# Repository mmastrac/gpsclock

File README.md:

========

Simple GPS clock project based on simple components from Adafruit and eBay. This consists of a number of components:

  * A backpack for the Adafruit KWA-221 2.3" digit based on the TLC-5920NT (KiCad PCB project)

  * An Arduino project that reads GPS time from the Adafruit GPS adapter and pushes it out to backpack

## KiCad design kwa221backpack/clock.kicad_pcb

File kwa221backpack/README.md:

TODO:

  * Contribute TLC-5940NT back to open-projects
  * Move all routed traces underneath footprint of LED

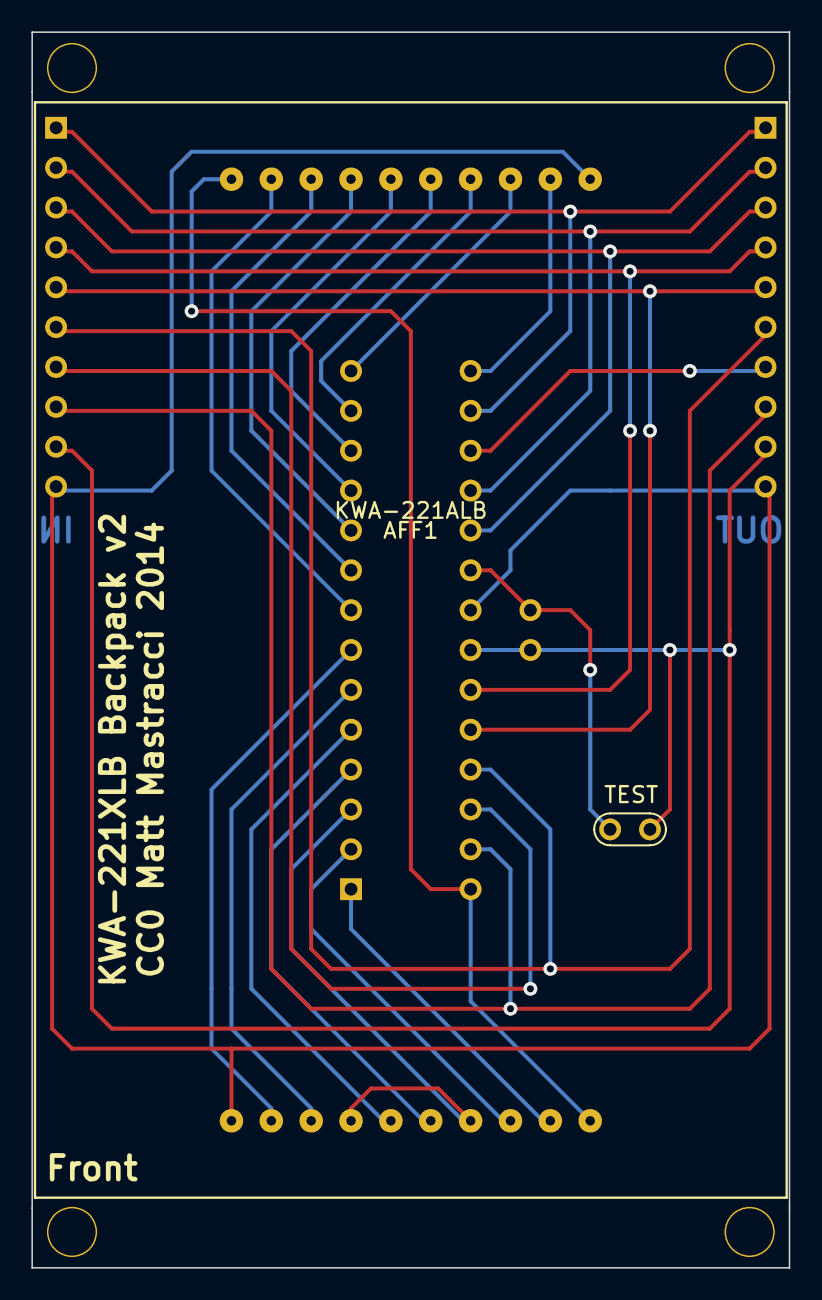
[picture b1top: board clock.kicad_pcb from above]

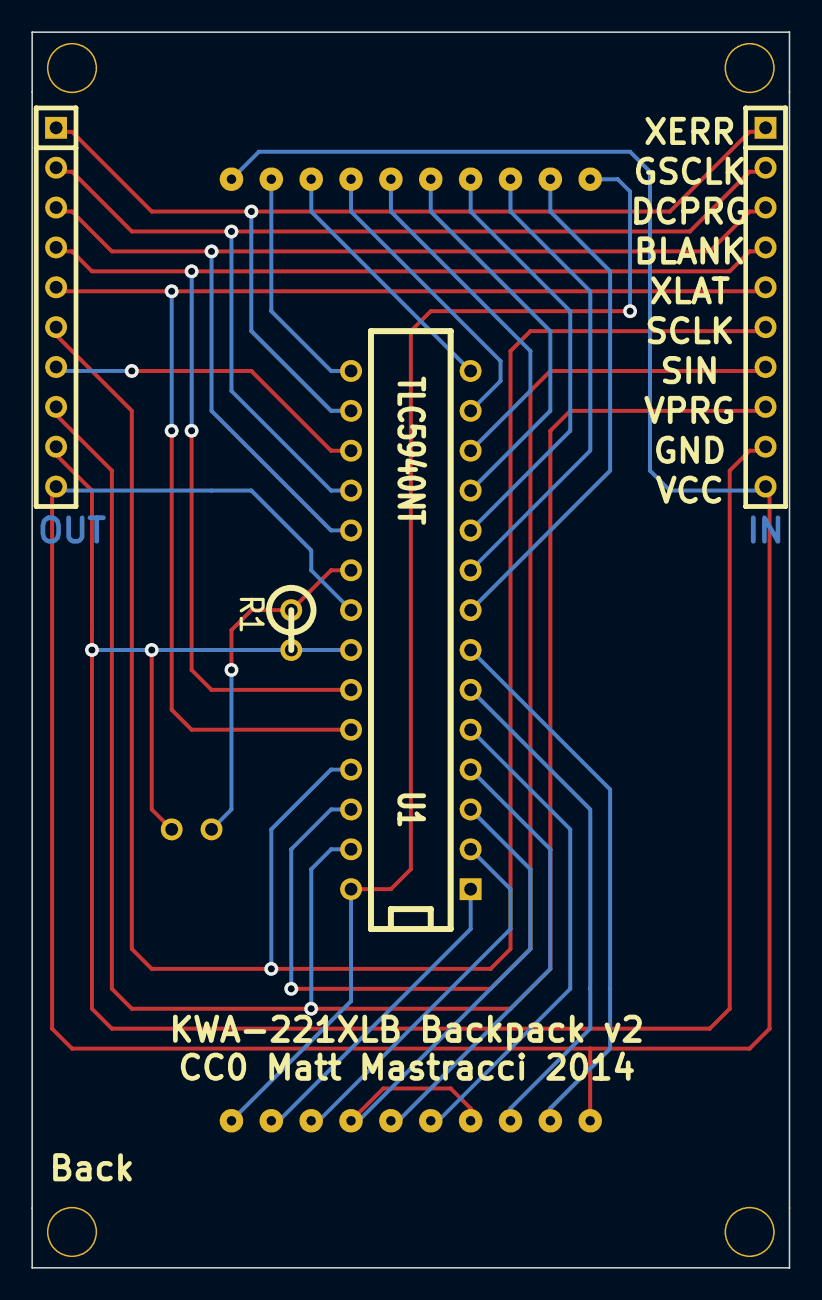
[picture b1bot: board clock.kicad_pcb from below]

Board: 2 copper layers, 48.3 x 78.7 mm, 10 parts (4 on the bottom side), 28 nets.

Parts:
AFF1: KWA-221ALB; KWA-221
IN1: SIL-10
MH1, MH2, MH3, MH4: MOUNTING_HOLE; 3MM_HOLE
OUT1: SIL-10
R1: R; R1
U1: TLC5940NT; DIP-28__300
W1: TEST; TEST_POINT_2PADS

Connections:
/BLANK: IN1.4, OUT1.4, U1.23
/D0: AFF1.10, AFF1.20, U1.28
/D1: AFF1.9, U1.1
/D2: AFF1.8, U1.2
/D3: AFF1.4, AFF1.7, U1.3
/D4: AFF1.6, U1.4
/D5: AFF1.5, U1.5
/D6: AFF1.3, U1.6
/D7: AFF1.2, U1.7
/D8: AFF1.19, U1.8
/D9: AFF1.18, U1.9
/D10: AFF1.17, U1.10
/D11: AFF1.16, U1.11
/D12: AFF1.15, U1.12
/D13: AFF1.14, U1.13
/D14: AFF1.13, U1.14
/D15: AFF1.12, U1.15
/DCPRG: IN1.3, OUT1.3, U1.19
/GSCLK: IN1.2, OUT1.2, U1.18
/SCLK: IN1.6, OUT1.6, U1.25
/SIN: IN1.7, U1.26
/SOUT: OUT1.7, U1.17
/VPRG: IN1.8, OUT1.8, U1.27
/XERR: IN1.1, OUT1.1, U1.16
/XLAT: IN1.5, OUT1.5, U1.24
GND: IN1.9, OUT1.9, R1.2, U1.22, W1.1
IREF: R1.1, U1.20, W1.2
VCC: AFF1.1, AFF1.11, IN1.10, OUT1.10, U1.21

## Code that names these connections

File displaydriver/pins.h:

#pragma once

/*
	Attiny85 pinouts:

	           +----+ 
	RESET   5 -|o   |-   VCC 
	DATAOUT 3 -|    |- 2 SIN
	DATAIN  4 -|    |- 1 GSCLK/SCLK
	GND       -|    |- 0 BLANK/XLAT
		       +----+
*/


// BLANK + XLAT
#define BLANK_PORT B
#define BLANK_PIN 0

// GSCLK + SCLK
#define GSCLK_PORT B
#define GSCLK_PIN 1

// SIN
#define SIN_PORT B
#define SIN_PIN 2

// DATAIN
#define DATAIN_PORT B
#define DATAIN_PIN 4

// DATAOUT
#define DATAOUT_PORT B
#define DATAOUT_PIN 3

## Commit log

2014-09-09 First (nearly-routed) version of a board for the Adafruit 2.3" display
2014-09-09 Move these files to a subdirectory
2014-09-09 README changes
2014-09-09 Remove .bak files Add README with a TODO
2014-09-09 Remove more backup files Remove unused exported component
2014-09-09 Adding a .gitignore for KiCad bak files
2014-09-09 Re-generate PCB
2014-09-09 Re-order pins on header to simplify chip routing
2014-09-09 Moving the headers up -- not sure I like this
2014-09-09 Moving the top traces closer to the IC
2014-09-09 Managed to route all the traces under the LED
2014-09-09 More tweaking, allow 3D to render better
2014-09-10 Export Gerber/VRML
2014-09-10 SVG/cleanup
2014-09-10 pcb png
2014-09-10 Adding really basic Arduino test sketch
2014-09-10 Half size image
2014-09-10 Clean out old VRML/SVG files. Clean up PCB.
2014-09-10 Generate gerber files. Adding fontmaker
2014-09-10 Lay out the font for A-Z, a-z, 0-9 and some various symbols
2014-09-10 Add more letters.
2014-09-11 Add a viewer, flesh out the character set
2014-09-11 Add a logo
2014-09-11 Try again
2014-09-11 Add screenshot for arduino, resize images
2014-09-11 The 7 was bugging me. Check in a compiling version of the GPS prototype.
2014-09-11 Tweak digits
2014-09-11 Adding framework for tzgen -- the tools required to generate tz data for auto-setting tz
2014-09-11 Doing some analysis on the TZ file to see what sort of compression might be feasible
2014-09-12 In-progress commit while testing compression (this is ugly, don't look)
2014-09-12 Rename package
2014-09-12 Started moving encoding into a class structure
2014-09-12 Now packing the TZ map into ~190kB (although unpacking hasn't been tested\!)
2014-09-12 Clean up old optimizer cruft
2014-09-14 Compress the world data to < 120k
2014-09-14 Ensure that we minimize ref chains where possible
2014-09-14 Ensure we can round-trip packed int lists
2014-09-14 Add a better heuristic for creating full-encoding lines
2014-10-11 Update schematic for v2: mounting holes and test point to measure iref resistor
2014-10-11 Moving outputs to a v1 directory so we can eventually generate a v2
2014-10-17 Adding proof-of-concept TLC5940 bit-bang
2014-10-18 Moving GS data into an array
2014-10-18 Rewrite macros to reduce boilerplate. Use a timer for the source of the LED brightness.
2014-10-18 .gitignore for avr files
2014-10-19 Get this working with 32 channels of goodness
2014-10-19 Removing the last of the glitches by allowing the clocked-in data to settle
2014-10-19 Hooking up the font
2014-10-20 Add serial input
2014-10-20 Ensure we can read two chars back-to-back
2014-10-20 Add the beginning of a software UART
2014-10-20 Cleaning up source
2014-10-20 Adding a protocol, modify serial ring buffer to return # of bytes available
2014-10-20 Off-by-one error in the serial code
2014-10-21 Re-working serial a bit, adding a new command for scrolling
2014-11-07 Adding self-calibration over serial
2014-11-09 Serial send and receive on interrupts
2014-11-09 Serial send/receive *mostly* working now
2014-11-09 Add spurious pin change detected
2014-11-09 Serial is occasionally returning FF for receive -- unsure why, but it's getting better
2014-11-09 By making TIMER1_OVF less expensive, serial becomes more reliable
2014-11-09 Remove unnecessary cli/sei
2014-11-09 Adding a command-line tester for more rapid development
2014-11-10 Rewrite timers to use lock-free approach
2016-04-03 Correct fuse settings
